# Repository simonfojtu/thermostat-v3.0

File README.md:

# thermostat-v3.0
esp8266-12-q based thermostat

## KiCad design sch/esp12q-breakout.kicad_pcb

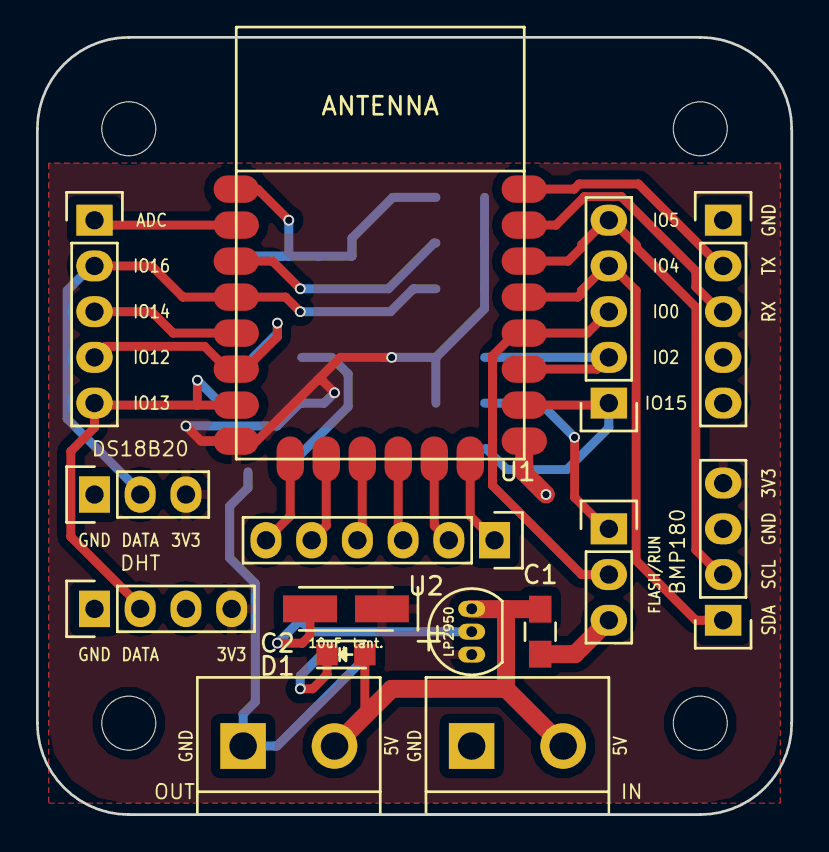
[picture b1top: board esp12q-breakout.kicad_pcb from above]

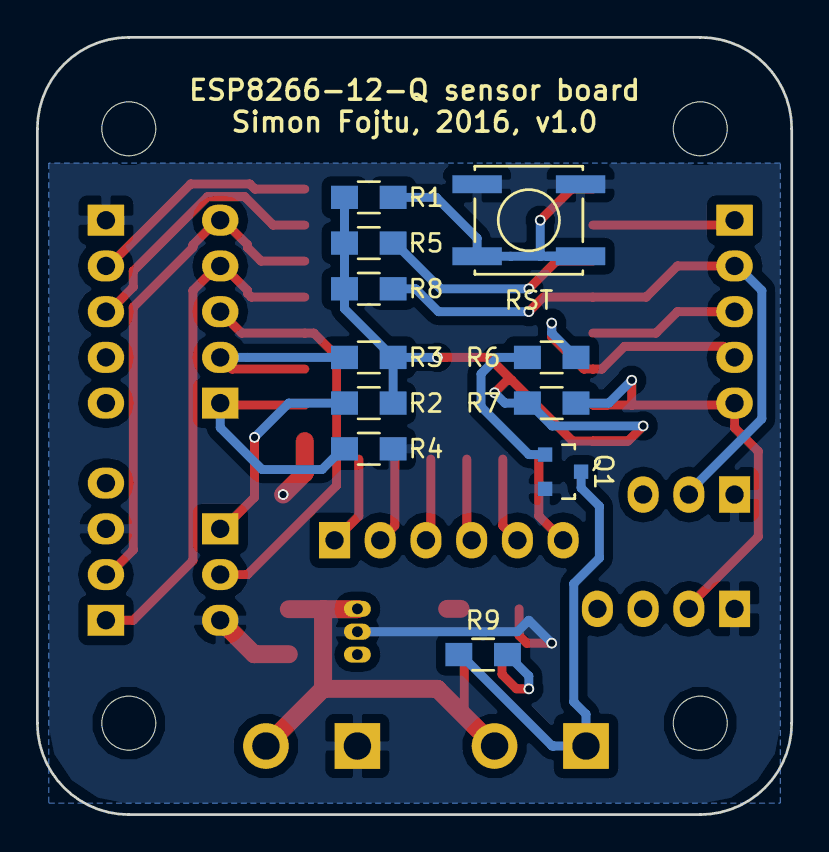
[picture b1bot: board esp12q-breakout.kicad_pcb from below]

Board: 2 copper layers, 41.9 x 43.2 mm, 26 parts (11 on the bottom side), 27 nets.

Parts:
C1: 1uF, cer.; C_0805_HandSoldering
C2: 10uF, tant.; TantalC_SizeA_EIA-3216_HandSoldering
D1: LED; LED-0805
P1, P3: CONN_01X05; Pin_Header_Straight_1x05
P2: FLASH/RUN; Pin_Header_Straight_1x03
P4: SERIAL; Pin_Header_Straight_1x05
P5: 5V IN; bornier2
P6: DS18B20; Pin_Header_Straight_1x03
P7: BMP180; Pin_Header_Straight_1x04
P8: OUT max 100mA; bornier2
P9: CONN_01X04; Pin_Header_Straight_1x04
P10: CONN_01X06; Pin_Header_Straight_1x06
Q1: BC847; SOT-23
R1, R2, R5: 10k; R_0805_HandSoldering
R3, R4: 0R; R_0805_HandSoldering
R6: 1k; R_0805_HandSoldering
R7, R8: 4k7; R_0805_HandSoldering
R9: 220; R_0805_HandSoldering
RST: SW_PUSH; SW_SPST_EVPBF
U1: ESP-12-Q; esp8266-12-q
U2: LP2950; TO-92_Inline_Narrow_Oval

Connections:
+3V3: C2.1, P6.3, P7.4, P9.4, R1.1, R2.1, R3.2, R5.1, R7.1, R8.1, U1.8, U2.1
+5V: C1.1, D1.2, P5.2, P8.2, U2.3
/ADC: P1.1, U1.2
/BMP_SCL: P3.5, P7.2, U1.20
/BMP_SDA: P3.4, P7.1, U1.19
/CTRL_OUT: P1.4, R6.2, U1.6
/DHT11_DATA: P1.5, P9.2, R7.2, U1.7
/DS18B20_DATA: P1.2, P6.2, R8.2, U1.4
/EN: R5.2, U1.3
/GPIO0: P2.2, P3.3, U1.18
/GPIO2: P3.2, R3.1, U1.17
/GPIO14: P1.3, U1.5
/GPIO15: P3.1, R4.1, U1.16
/RST: R1.2, RST.1, U1.1
/RX: P4.3, U1.21
/TX: P4.2, U1.22
GND: C1.2, C2.2, P2.3, P4.1, P5.1, P6.1, P7.3, P9.1, Q1.2, R4.2, RST.2, U1.15, U2.2
unnamed: D1.1, R9.1
unnamed: P2.1, R2.2
unnamed: P8.1, Q1.3, R9.2
unnamed: P10.1, U1.14
unnamed: P10.2, U1.13
unnamed: P10.3, U1.12
unnamed: P10.4, U1.11
unnamed: P10.5, U1.10
unnamed: P10.6, U1.9
unnamed: Q1.1, R6.1

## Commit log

2016-01-01 schematics v1.0
